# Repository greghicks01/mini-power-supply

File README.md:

# mini-power-supply
Simple mains based supply with dual rail unreg, dual rail adj reg and 5V with mains derived 100Hz Clock for basic logic chip breadboarding

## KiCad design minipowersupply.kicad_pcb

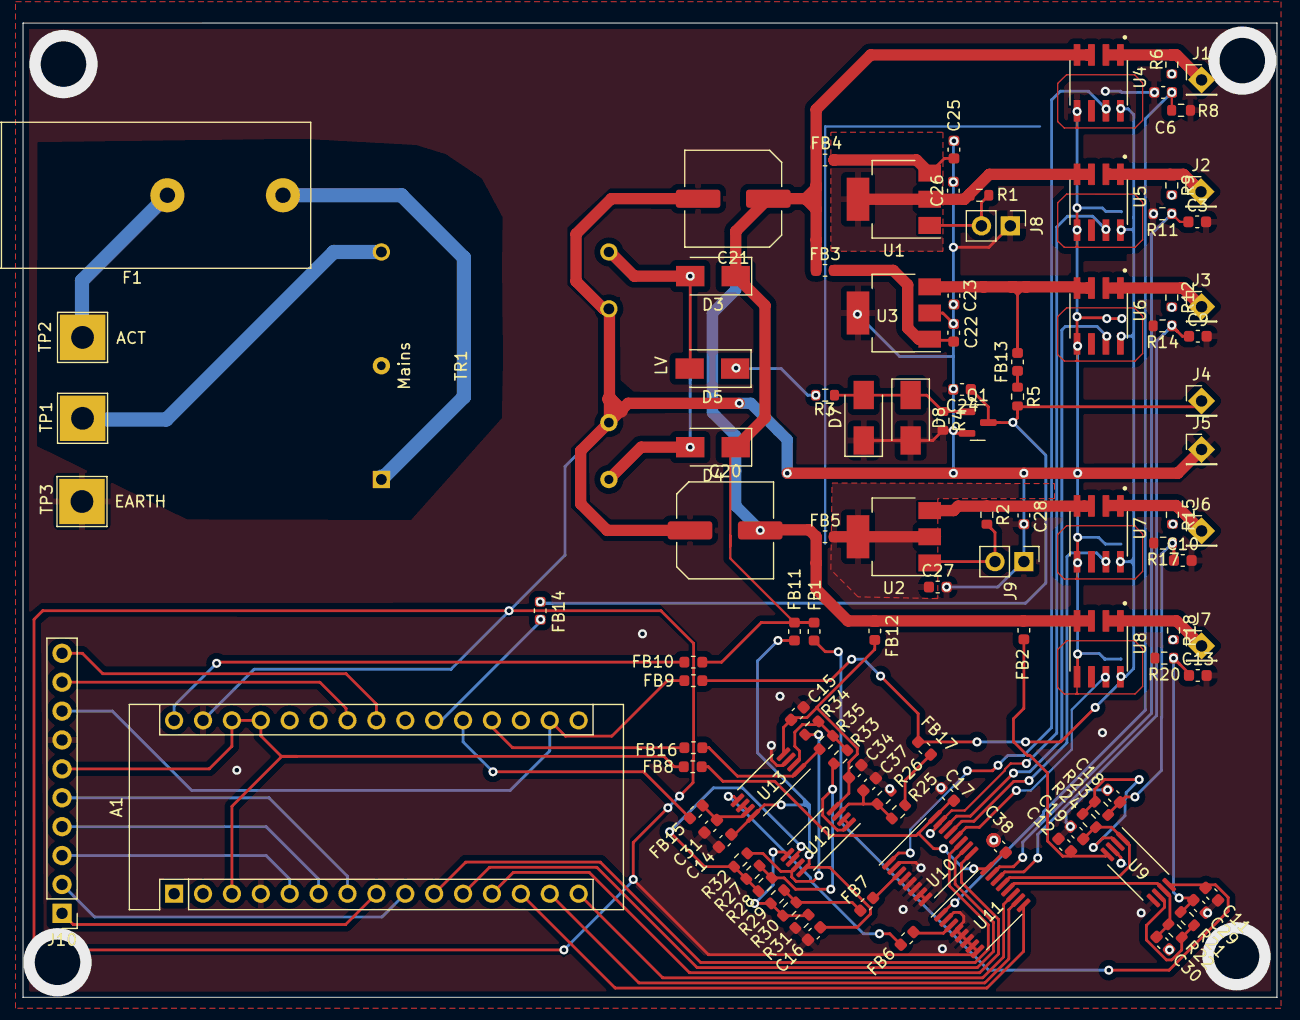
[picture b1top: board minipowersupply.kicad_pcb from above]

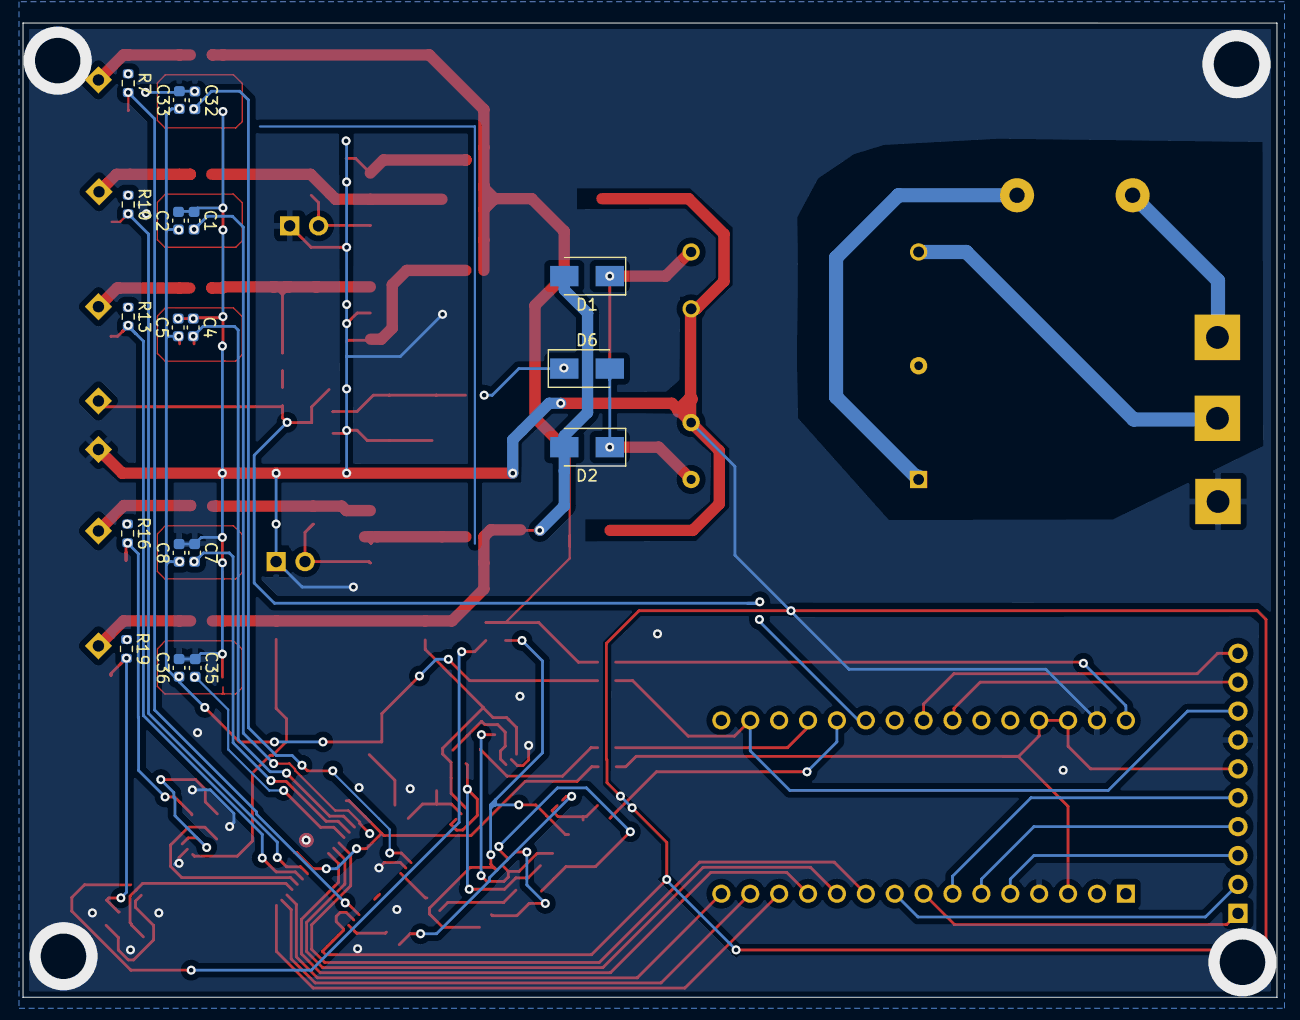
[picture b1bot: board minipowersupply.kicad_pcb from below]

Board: 2 copper layers, 110.2 x 85.7 mm, 128 parts (18 on the bottom side), 82 nets.

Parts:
A1: Arduino_Nano_v3.x; Arduino_Nano
C1, C2, C3, C4, C5, C6, C7, C8, C9, C10, C11, C12, C13, C14, C15, C16, C17, C18, C19, C22, C23, C24, C25, C27, C29, C30, C31, C32, C33, C34, C35, C36, C37, C38: 0.1uF; C_0603_1608Metric
C20, C21: 150uF; C_Elec_8x6.2
C26, C28: 1uF; C_0603_1608Metric
D1, D2, D3, D4, D5, D6, D7, D8: S1K-13-F; D_SMA
F1: Fuse; Fuseholder_Cylinder-5x20mm_Bulgin_FX0457_Horizontal_Closed
FB1, FB2, FB3, FB4, FB5, FB6, FB7, FB8, FB9, FB10, FB11, FB12, FB13, FB14, FB15, FB16, FB17: FerriteBead_Small; L_0603_1608Metric
J1, J2, J3, J4, J5, J6, J7: Conn_01x01_Female; PinHeader_1x01_P2.54mm_Vertical
J8, J9: Conn_01x02_Female; PinHeader_1x02_P2.54mm_Vertical
J10: Conn_01x08_Male; PinHeader_1x10_P2.54mm_Vertical
Q1: BC817; SOT-23
R1, R2: 240; R_0603_1608Metric
R3: 4.420k; R_0603_1608Metric
R4: 698; R_0603_1608Metric
R5: 410; R_0603_1608Metric
R6, R7, R8, R9, R10, R11, R12, R13, R14, R15, R16, R17, R18, R19, R20, R21, R22, R23, R24, R25, R26, R27, R28, R29, R30, R33, R34, R35: 10k 0.01%; R_0603_1608Metric
R31, R32: 100k 0.01%; R_0603_1608Metric
TP1, TP2, TP3: TestPoint; TestPoint_THTPad_4.0x4.0mm_Drill2.0mm
TR1: TRANSF3; vtxtfr
U1: LM317_TO-220; SOT-223-3_TabPin2
U2: LM337_TO220; SOT-223-3_TabPin2
U3: LM7805_TO220; SOT-223-3_TabPin2
U4, U5, U6, U7, U8: ACS70331EOLCTR-2P5U3; SOIC127P600X175-8N
U9, U12, U13: LM358; TSSOP-8_4.4x3mm_P0.65mm
U10, U11: 74HC4051; TSSOP-16_4.4x5mm_P0.65mm

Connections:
3V3: C2.1, C5.1, C8.1, C33.1, C36.1, FB9.1, FB17.1, U4.8 (VCC), U5.8 (VCC), U6.8 (VCC), U7.8 (VCC), U8.8 (VCC)
/Clock and TTL/Ck_Out: C24.1, FB14.1, J4.1, Q1.3 (C), R5.2
/Clock and TTL/HalfSineIn: D5.1 (K), D6.1 (K), R3.2
/Clock and TTL/V5Out: C23.1, FB13.2, U3.3 (VO), U6.3 (IP-), U6.4 (IP-)
/DualAdj/Vreg+: C26.1, R1.1, U1.2 (VO), U5.3 (IP-), U5.4 (IP-)
/DualAdj/Vreg-: C28.2, R2.1, U2.3 (VO), U7.3 (IP-), U7.4 (IP-)
/I V Sensor, Mux and output/5 Current/Vout: J3.1, R12.1, U6.1 (IP+), U6.2 (IP+)
/I V Sensor, Mux and output/A0: A1.10 (D7), U10.11 (S0)
/I V Sensor, Mux and output/A1: A1.11 (D8), U10.10 (S1)
/I V Sensor, Mux and output/A2: A1.12 (D9), U10.9 (S2)
/I V Sensor, Mux and output/A3: A1.13 (D10), U11.9 (S2)
/I V Sensor, Mux and output/A4: A1.14 (D11), U11.10 (S1)
/I V Sensor, Mux and output/A5: A1.15 (D12), U11.11 (S0)
/I V Sensor, Mux and output/A+ Current/Vout: J2.1, R9.1, U5.1 (IP+), U5.2 (IP+)
/I V Sensor, Mux and output/A- Current/Vout: J6.1, R15.1, U7.1 (IP+), U7.2 (IP+)
/I V Sensor, Mux and output/A- Unity Inverter/Ain: C10.1, C18.1, R16.2, R17.1, R23.1
/I V Sensor, Mux and output/Amp: FB7.1, U10.3 (A)
/I V Sensor, Mux and output/I5: C4.2, U6.7 (VIOUT), U10.14 (A1)
/I V Sensor, Mux and output/IA+: C1.2, U5.7 (VIOUT), U10.15 (A2)
/I V Sensor, Mux and output/IA-: C7.2, U7.7 (VIOUT), U10.13 (A0)
/I V Sensor, Mux and output/IU+: C32.2, U4.7 (VIOUT), U10.1 (A4)
/I V Sensor, Mux and output/IU-: C35.2, U8.7 (VIOUT), U10.12 (A3)
/I V Sensor, Mux and output/U+ Current/Vout: J1.1, R6.1, U4.1 (IP+), U4.2 (IP+)
/I V Sensor, Mux and output/U- Current/Vout: J7.1, R18.1, U8.1 (IP+), U8.2 (IP+)
/I V Sensor, Mux and output/U- Unity Inverter/Ain: C13.1, C29.1, R19.2, R20.1, R21.1
/I V Sensor, Mux and output/V5+: C9.1, R13.2, R14.1, U11.14 (A1)
/I V Sensor, Mux and output/VA+: C3.1, R10.2, R11.1, U11.15 (A2)
/I V Sensor, Mux and output/VA-: C19.1, R24.2, U9.1, U11.13 (A0)
/I V Sensor, Mux and output/VU+: C6.1, R7.2, R8.1, U11.1 (A4)
/I V Sensor, Mux and output/VU-: C30.1, R22.2, U9.7, U11.12 (A3)
/I V Sensor, Mux and output/Volt: FB6.1, U11.3 (A)
/Measure/SCL: A1.24 (A5), J10.9
/Measure/SDA: A1.23 (A4), J10.10
GNDREF: A1.4 (GND), A1.29 (GND), C1.1, C2.2, C3.2, C4.1, C5.2, C6.2, C7.1, C8.2, C9.2, C10.2, C11.2, C12.2, C13.2, C14.2, C15.2, C16.2, C17.1, C18.2, C19.2, C20.1, C21.2, C22.2, C23.2, C24.2, C25.2, C26.2, C27.2, C28.1, C29.2, C30.2, C31.1, C32.1, C33.2, C34.2, C35.1, C36.2, C37.2, C38.1, D7.1 (A), D8.2 (K), J5.1, J8.1, J9.1, J10.7, Q1.2 (E), R4.2, R8.2, R11.2, R14.2, R17.2, R20.2, R26.2, R31.2, TP3.1, TR1.4, TR1.5, U3.2 (GND), U4.5 (GND), U5.5 (GND), U6.5 (GND), U7.5 (GND), U8.5 (GND), U9.3 (+), U9.5 (+), U10.2 (A6), U10.4 (A7), U10.5 (A5), U10.6 (~E), U10.7 (VEE), U10.8 (GND), U11.2 (A6), U11.4 (A7), U11.5 (A5), U11.6 (~E), U11.7 (VEE), U11.8 (GND), U13.3 (+)
unnamed: A1.5 (D2), J10.3
unnamed: A1.6 (D3), J10.4
unnamed: A1.7 (D4), J10.5
unnamed: A1.8 (D5), J10.1
unnamed: A1.9 (D6), J10.2
unnamed: A1.17 (3V3), FB9.2, J10.8
unnamed: A1.19 (A0), FB16.2
unnamed: A1.20 (A1), FB15.2
unnamed: A1.21 (A2), FB14.2
unnamed: A1.3 (~RESET), A1.27 (+5V), A1.28 (~RESET), FB8.2, J10.6
unnamed: A1.30 (VIN), FB10.2
unnamed: C11.1, FB1.2, U9.8 (V+)
unnamed: C12.1, FB2.2, U9.4 (V-)
unnamed: C14.1, C16.1, FB11.2, U12.8 (V+), U13.8 (V+)
unnamed: C15.1, C34.1, FB12.1, U12.4 (V-), U13.4 (V-)
unnamed: C22.1, FB3.2, U3.1 (VI)
unnamed: C25.1, FB4.2, U1.3 (VI)
unnamed: C27.1, FB5.2, U2.2 (VI)
unnamed: C31.2, FB15.1, U13.6 (-), U13.7
unnamed: C37.1, R25.2, R26.1, U12.3 (+)
unnamed: D1.1 (K), D3.2 (A), D5.2 (A), TR1.3
unnamed: D2.1 (K), D4.2 (A), D6.2 (A), TR1.6
unnamed: D7.2 (K), D8.1 (A), Q1.1 (B), R3.1, R4.1
unnamed: F1.1, TR1.1
unnamed: F1.2, TP2.1
unnamed: FB6.2, U13.5 (+)
unnamed: FB7.2, R29.2, R30.2
unnamed: FB13.1, R5.1
unnamed: FB16.1, R35.2, U13.1
unnamed: FB17.2, R25.1
unnamed: J8.2, R1.2, U1.1 (ADJ)
unnamed: J9.2, R2.2, U2.1 (ADJ)
unnamed: R6.2, R7.1
unnamed: R9.2, R10.1
unnamed: R12.2, R13.1
unnamed: R15.2, R16.1
unnamed: R18.2, R19.1
unnamed: R21.2, R22.1, U9.6 (-)
unnamed: R23.2, R24.1, U9.2 (-)
unnamed: R27.1, R28.1, R33.1, U12.1, U12.2 (-)
unnamed: R27.2, R28.2, R32.2, U12.6 (-)
unnamed: R29.1, R30.1, R31.1, U12.5 (+)
unnamed: R32.1, R34.1, U12.7
unnamed: R33.2, R34.2, R35.1, U13.2 (-)
unnamed: TP1.1, TR1.2
V5: C17.2, C38.2, FB8.1, U10.16 (VCC), U11.16 (VCC)
VUnreg+: C21.1, D3.1 (K), D4.1 (K), FB1.1, FB3.1, FB4.1, FB10.1, FB11.1, U4.3 (IP-), U4.4 (IP-)
VUnreg-: C20.2, D1.2 (A), D2.2 (A), FB2.1, FB5.1, FB12.2, U8.3 (IP-), U8.4 (IP-)

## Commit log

2022-10-01 Updates with latest current and voltage sensor plus arduino to measure and display - will remove extra features for current simple production
2022-10-01 Reduced to simplest layout structure in readiness for PCBWay production
2022-10-02 altered simple board layout to improve panelisation
2022-10-02 Simple (#1)
    * Updates with latest current and voltage sensor plus arduino to measure and display - will remove extra features for current simple production
    * Reduced to simplest layout structure in readiness for PCBWay production
    * altered simple board layout to improve panelisation
2022-10-02 inor updates
2022-10-06 finalising diagram
2022-10-06 minor update
2022-10-06 sorting out earths and making measure mux board
2022-10-08 last TH mounting board
2022-10-08 all SMD components going into boards
2022-10-09 new board with SMD
2022-10-09 New single board with all SMD in progress
2022-10-17 Updated improved board for all SMD
2022-10-17 added PDF schematic and images of board to date
2022-10-20 Refined board and kerned size down
2022-10-25 further refining board size, adding rotary encoder and OLED display
2022-10-27 repositioned signal wires and started mapping OLED and rotary encoder
2022-10-31 adding diff and summing amps to scale amp inputs
2022-10-31 Added current Board and Schematic PDF
2022-11-07 added new op amps and used automated traces due to complexity
2022-11-08 fixed last ground plane connection, added ground ring for power output ground
2022-11-08 improved earthing and created ring track to isolate supply from display electronics
2022-11-10 small position adjustments to attain required spacing
2022-11-17 new EMC-EMI layout with improved suppression
2022-11-23 updates with foot print guard rings
2022-11-25 New board layout
2022-12-07 working on MUX and pre-amp layout
2022-12-20 mux and opamp layouts completed and new ext conn to display
2023-01-13 updated with extra filtering and guard ring placement
